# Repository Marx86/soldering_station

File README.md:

# soldering_station
Soldering Station

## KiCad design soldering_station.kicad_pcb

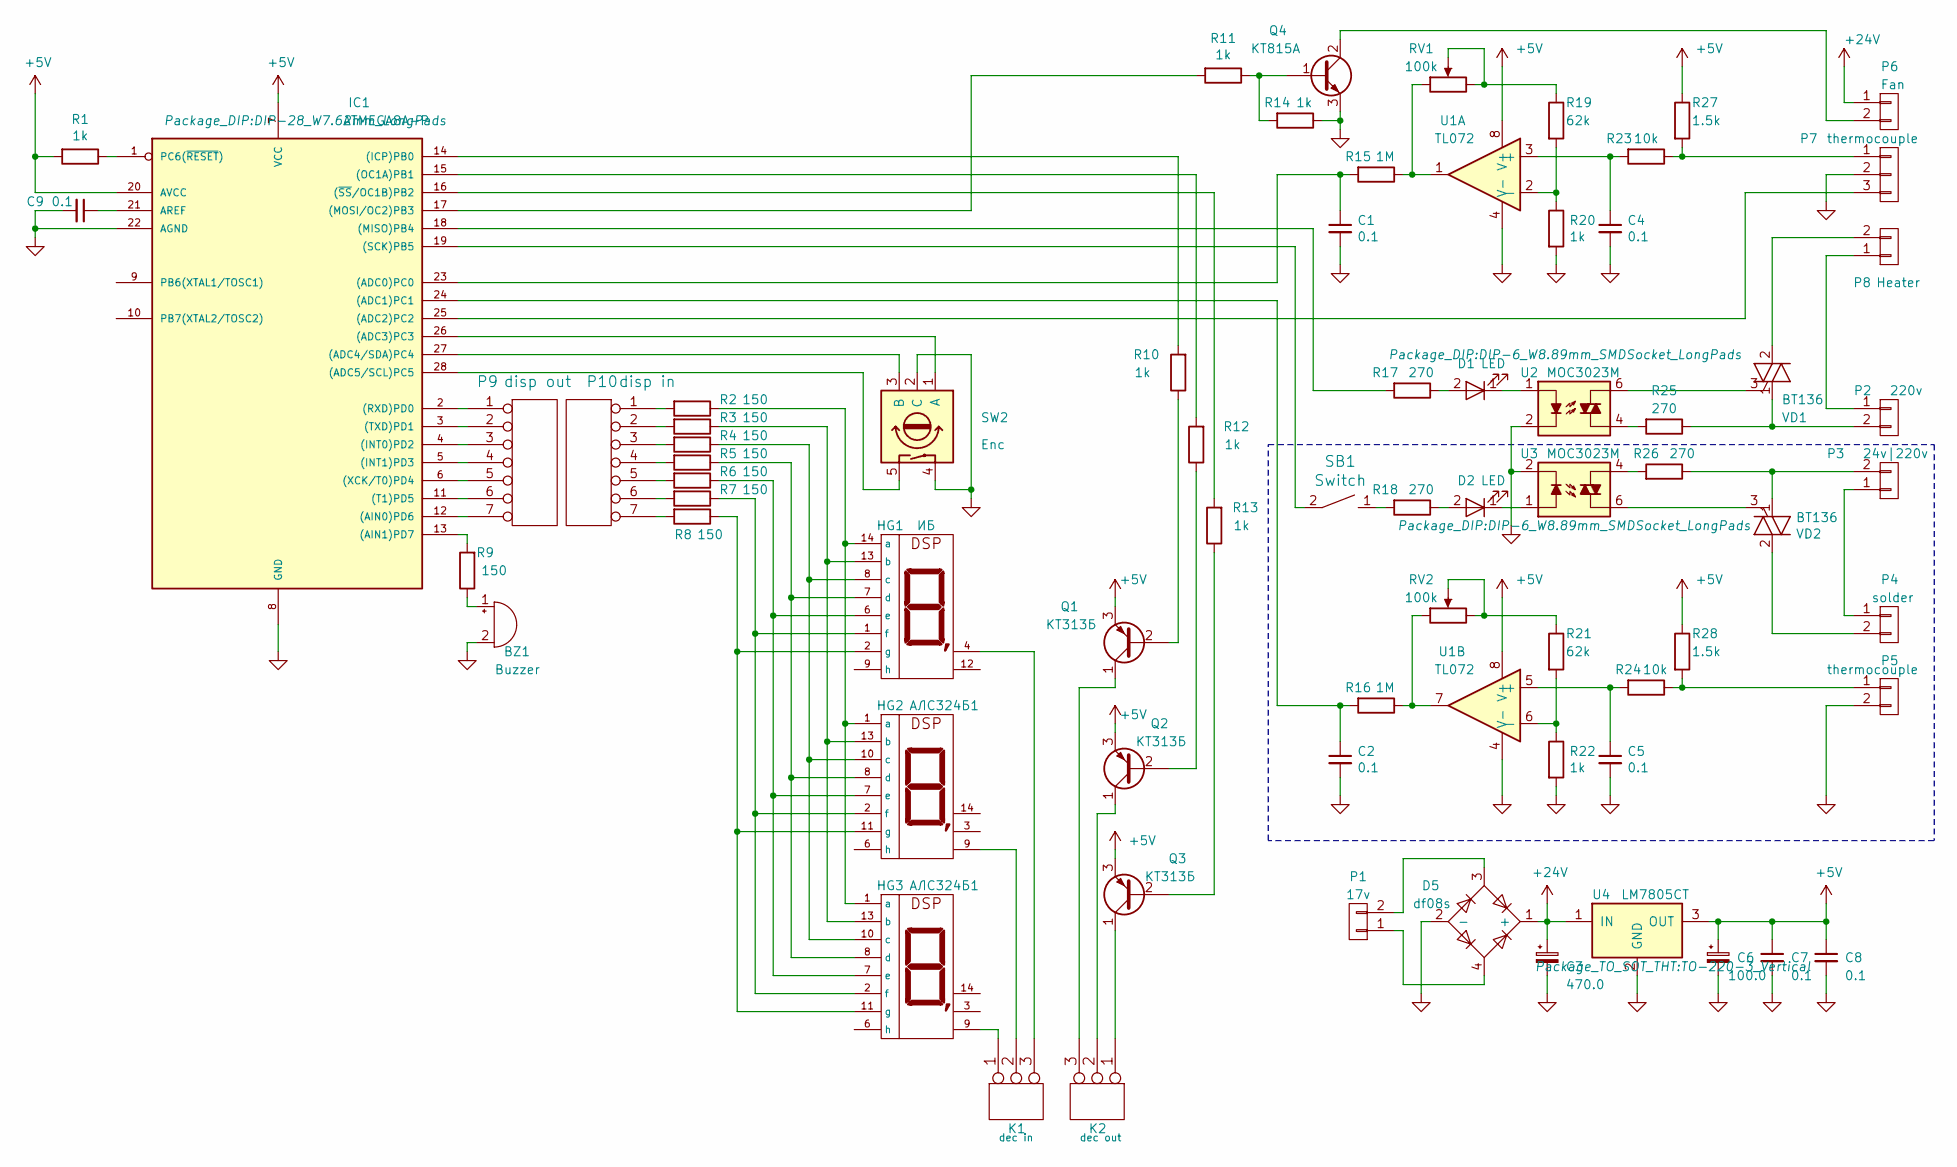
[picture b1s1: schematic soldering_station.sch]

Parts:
BZ1: Buzzer; Buzzer_12x9.5RM7.6
C1, C2, C4, C5, C7, C8, C9: 0.1; C_0805_2012Metric
C3: 470.0; CP_Radial_D8.0mm_P3.80mm
C6: 100.0; CP_Radial_D5.0mm_P2.50mm
D1, D2: LED; LED_D5.0mm
D5: df08s; Oscillator_SMD_SeikoEpson_SG8002JA-4Pin_14.0x8.7mm
HG1: ИБ; иб
HG2, HG3: АЛС324Б1; DIP-14_W7.62mm
IC1: ATMEGA8A-P; DIP-28_W7.62mm_LongPads
K1: dec in; PinHeader_1x03_P2.54mm_Vertical
K2: dec out; PinHeader_1x03_P2.54mm_Vertical
P1: 17v; PinHeader_1x02_P2.54mm_Vertical
P2: 220v; SolderWirePad_1x02_P5.08mm_Drill1.5mm
P3: 24v|220v; SolderWirePad_1x02_P5.08mm_Drill1.5mm
P4: solder; SolderWirePad_1x02_P5.08mm_Drill1.5mm
P5: thermocouple; PinHeader_1x02_P2.54mm_Vertical
P6: Fan; PinHeader_1x02_P2.54mm_Vertical
P7: thermocouple; PinHeader_1x03_P2.54mm_Vertical
P8: Heater; SolderWirePad_1x02_P5.08mm_Drill1.5mm
P9: disp out; PinHeader_1x07_P2.54mm_Vertical
P10: disp in; PinHeader_1x07_P2.54mm_Vertical
Q1, Q2: КТ313Б; TO-92L_Wide
Q3: КТ313Б; TO-92_Wide
Q4: КТ815А; TO-126-3_Vertical
R1, R10, R11, R12, R13, R14, R20, R22: 1k; R_0805_2012Metric
R2, R3, R4, R5, R6, R7, R8, R9: 150; R_0805_2012Metric
R15, R16: 1M; R_0805_2012Metric
R17, R18, R25, R26: 270; R_0805_2012Metric
R19, R21: 62k; R_0805_2012Metric
R23, R24: 10k; R_0805_2012Metric
R27, R28: 1.5k; R_0805_2012Metric
RV1, RV2: 100k; Potentiometer_ACP_CA9-V10_Vertical
SB1: Switch; PinHeader_1x02_P2.54mm_Vertical
SW2: Enc; PinHeader_1x05_P2.54mm_Vertical
U1: TL072; DIP-8_W8.89mm_SMDSocket_LongPads
U2, U3: MOC3023M; DIP-6_W8.89mm_SMDSocket_LongPads
U4: LM7805CT; TO-220-3_Vertical
VD1, VD2: BT136; TO-220-3_Vertical

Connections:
+5V: C6.1, C7.1, C8.1, IC1.7 (VCC), IC1.20 (AVCC), Q1.3 (E), Q2.3 (E), Q3.3 (E), R1.2, R27.1, R28.1, U1.8 (V+), U4.3 (OUT)
+24V: C3.1, D5.1 (+), P6.1, U4.1 (IN)
GND: BZ1.2 (+), C1.2, C2.2, C3.2, C4.2, C5.2, C6.2, C7.2, C8.2, C9.2, D5.2 (-), IC1.8 (GND), IC1.22 (AGND), P5.2, P7.2, Q4.3 (E), R14.1, R20.2, R22.2, SW2.2 (C), SW2.4, U1.4 (V-), U2.2, U3.2, U4.2 (GND)
unnamed: BZ1.1 (-), R9.1
unnamed: C1.1, IC1.23 ((ADC0)PC0), R15.2
unnamed: C2.1, IC1.24 ((ADC1)PC1), R16.2
unnamed: C4.1, R23.2, U1.3 (+)
unnamed: C5.1, R24.2, U1.5 (+)
unnamed: C9.1, IC1.21 (AREF)
unnamed: D1.1 (K), U2.1
unnamed: D1.2 (A), R17.1
unnamed: D2.1 (K), U3.1
unnamed: D2.2 (A), R18.1
unnamed: D5.3, P1.2
unnamed: D5.4, P1.1
unnamed: HG1.1 (f), HG2.2 (f), HG3.2 (f), R7.1
unnamed: HG1.2 (g), HG2.11 (g), HG3.11 (g), R8.1
unnamed: HG1.4, K1.3
unnamed: HG1.6 (e), HG2.7 (e), HG3.7 (e), R6.1
unnamed: HG1.7 (d), HG2.8 (d), HG3.8 (d), R5.1
unnamed: HG1.8 (c), HG2.10 (c), HG3.10 (c), R4.1
unnamed: HG1.13 (b), HG2.13 (b), HG3.13 (b), R3.1
unnamed: HG1.14 (a), HG2.1 (a), HG3.1 (a), R2.1
unnamed: HG2.9, K1.2 (PM)
unnamed: HG3.9, K1.1
unnamed: IC1.1 (PC6(~RESET~)), R1.1
unnamed: IC1.2 ((RXD)PD0), P9.1
unnamed: IC1.3 ((TXD)PD1), P9.2
unnamed: IC1.4 ((INT0)PD2), P9.3
unnamed: IC1.5 ((INT1)PD3), P9.4
unnamed: IC1.6 ((XCK/T0)PD4), P9.5
unnamed: IC1.11 ((T1)PD5), P9.6
unnamed: IC1.12 ((AIN0)PD6), P9.7
unnamed: IC1.13 ((AIN1)PD7), R9.2
unnamed: IC1.14 ((ICP)PB0), R10.2
unnamed: IC1.15 ((OC1A)PB1), R12.2
unnamed: IC1.16 ((~SS~/OC1B)PB2), R13.2
unnamed: IC1.17 ((MOSI/OC2)PB3), R11.2
unnamed: IC1.18 ((MISO)PB4), R17.2
unnamed: IC1.19 ((SCK)PB5), SB1.2
unnamed: IC1.25 ((ADC2)PC2), P7.3
unnamed: IC1.26 ((ADC3)PC3), SW2.1 (A)
unnamed: IC1.27 ((ADC4/SDA)PC4), SW2.3 (B)
unnamed: IC1.28 ((ADC5/SCL)PC5), SW2.5
unnamed: K2.1, Q3.1 (C)
unnamed: K2.2 (PM), Q2.1 (C)
unnamed: K2.3, Q1.1 (C)
unnamed: P2.1, P8.1
unnamed: P2.2, R25.1, VD1.1 (A1)
unnamed: P3.1, P4.1
unnamed: P3.2, R26.1, VD2.1 (A1)
unnamed: P4.2, VD2.2 (A2)
unnamed: P5.1, R24.1, R28.2
unnamed: P6.2, Q4.2 (C)
unnamed: P7.1, R23.1, R27.2
unnamed: P8.2, VD1.2 (A2)
unnamed: P10.1, R2.2
unnamed: P10.2, R3.2
unnamed: P10.3, R4.2
unnamed: P10.4, R5.2
unnamed: P10.5, R6.2
unnamed: P10.6, R7.2
unnamed: P10.7, R8.2
unnamed: Q1.2 (B), R10.1
unnamed: Q2.2 (B), R12.1
unnamed: Q3.2 (B), R13.1
unnamed: Q4.1 (B), R11.1, R14.2
unnamed: R15.1, RV1.1, U1.1
unnamed: R16.1, RV2.1, U1.7
unnamed: R18.2, SB1.1
unnamed: R19.1, RV1.2, RV1.3
unnamed: R19.2, R20.1, U1.2 (-)
unnamed: R21.1, RV2.2, RV2.3
unnamed: R21.2, R22.1, U1.6 (-)
unnamed: R25.2, U2.4
unnamed: R26.2, U3.4
unnamed: U2.6, VD1.3 (G)
unnamed: U3.6, VD2.3 (G)

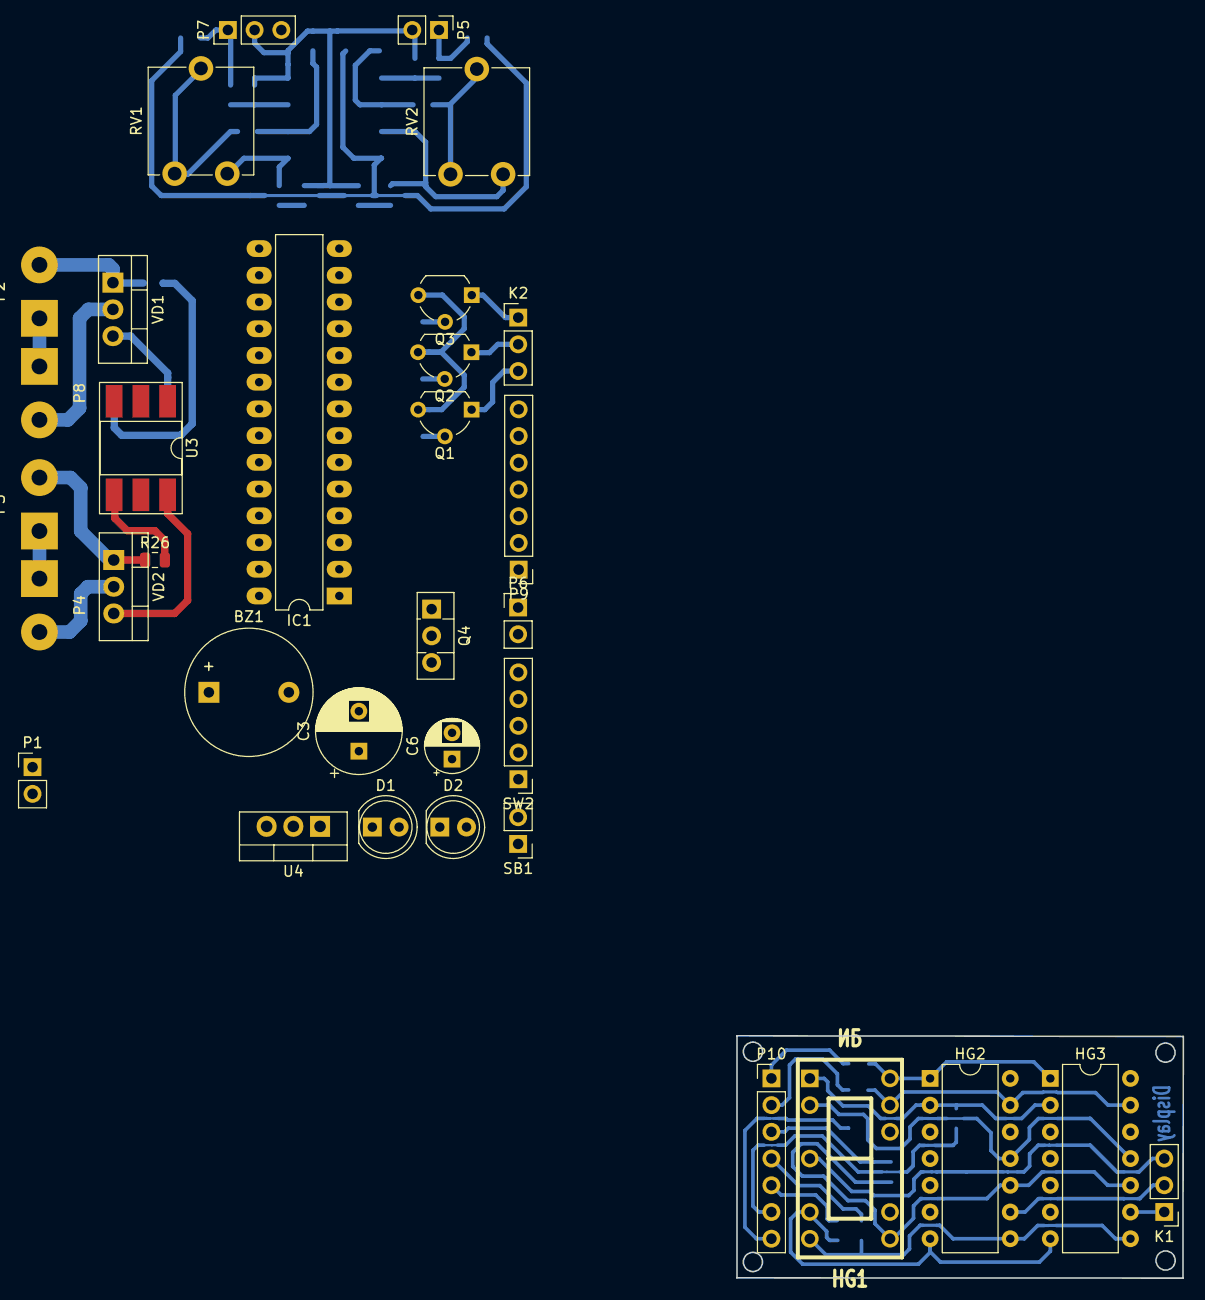
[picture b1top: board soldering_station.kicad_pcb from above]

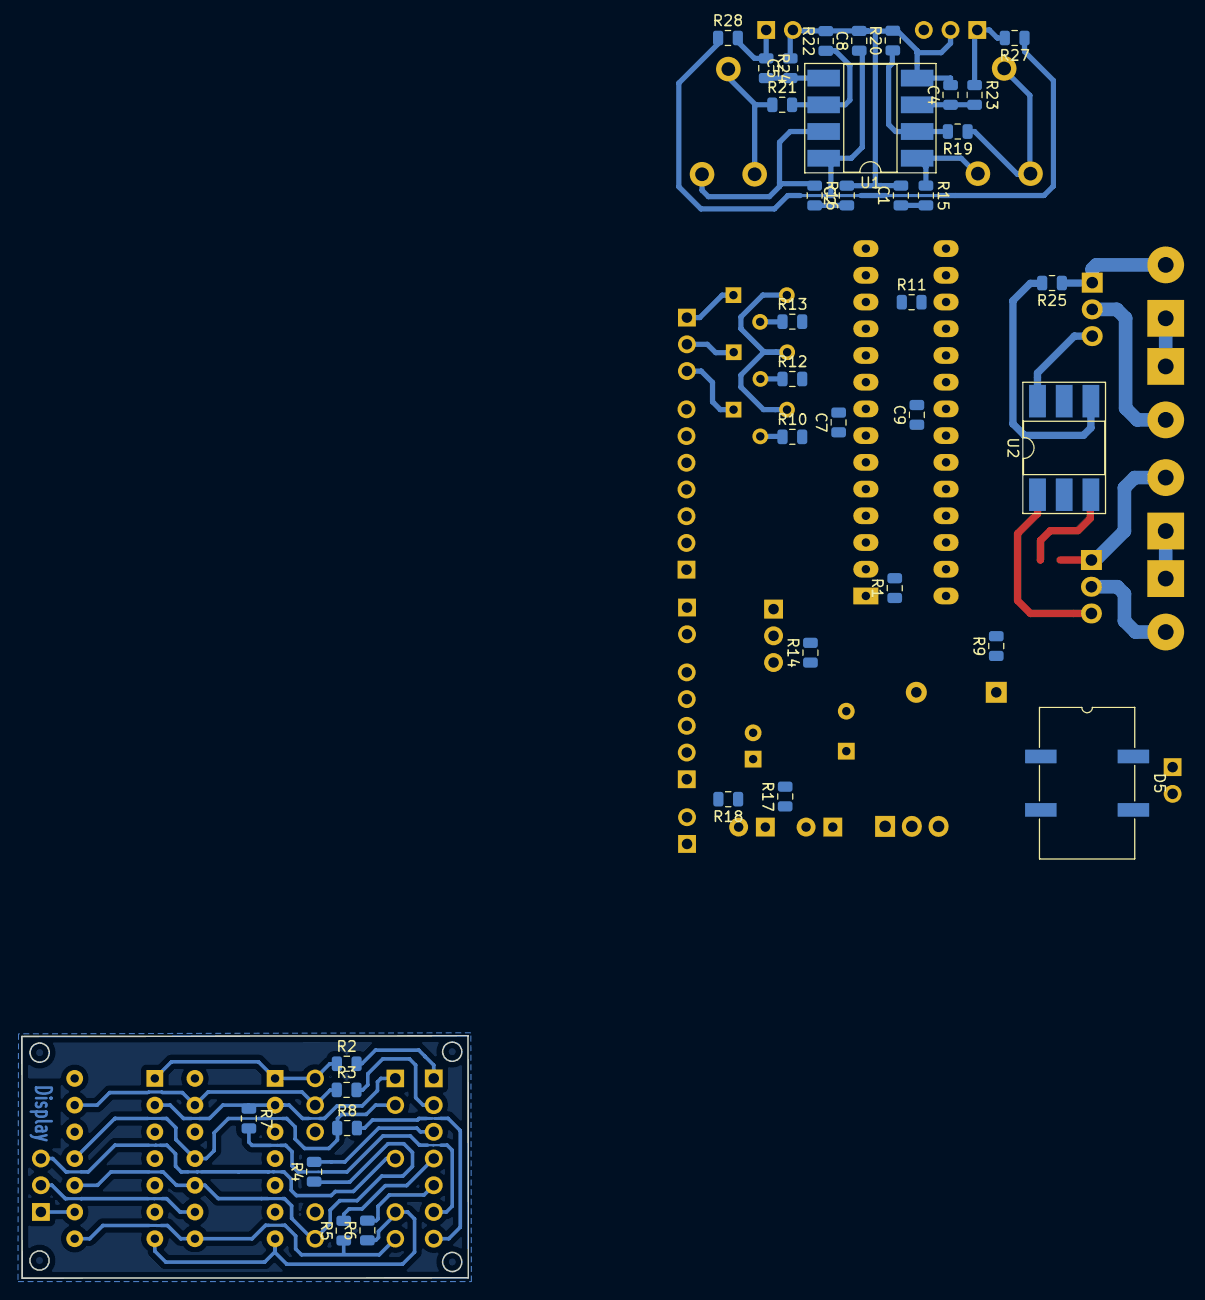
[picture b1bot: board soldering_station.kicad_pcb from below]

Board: 2 copper layers, 42.4 x 23.0 mm, 71 parts (37 on the bottom side), 78 nets.

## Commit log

2017-04-27 Add C rules to .gitignore
2017-04-27 Add circuit
2017-05-10 Change atmega48 to atmega8a
2017-05-10 Add encoder
2017-05-11 Add new libs and power regulator
2017-05-12 Add fan driver
2017-05-16 Add board
2017-05-22 Change heater gun connector
2017-05-24 Add 3D view
2017-05-24 Fix ADC ref pin
2017-08-08 Fix encoder
2018-01-23 Add size
2019-01-10 Fix board
2019-02-01 Add PCB PDFs
2019-11-06 Add connectors
2020-06-03 Change triac
2020-09-18 Display PCB
2021-05-18 Update PCB
